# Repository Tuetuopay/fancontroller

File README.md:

# FanController

*Creative naming?* What is this?

Rheobus project rooted from a simple problem: all my PC fans are DC only (the
three wire kind), but my motherboard only supports PWM*. And why buy a
commercial one? Let's make my own!

*Even if it does, shhhh! This is a good excuse for a project!

## Hardware

Simple PCB designed with Eagle. It can control up to 8 fans, with an STM32F103
as a brain. On the extra side, there is an LED for each channel, because
blinkenlights are cool. For communications, this is scarce: a USB port and
UART or I2C header.

The PCB is mostly finished, some refinements may be needed. It is well under
10cm x 10cm to be ordered on the cheap from the likes of DirtyPCB or JLCPCB.

All parts are SMD (except for headers and the one quartz), but do not go smaller
than 0603 resistors, easily solderable by hand. They can all be easily sourced
from Ebay.

## Software

This is not written yet. I plan on doing it with ChibiOS, just for kicks. It is
well supported on the STM32 platform, easy to use (once you accepted the fact
that documentation is almost nonexistent).

# Licence

```
THE BEER-WARE LICENSE (Revision 42):
tuetuopay at me dot com wrote this file. As long as you retain this notice you
can do whatever you want with this stuff. If we meet some day, and you think
this stuff is worth it, you can buy me a beer in return. Tuetuopay.
```

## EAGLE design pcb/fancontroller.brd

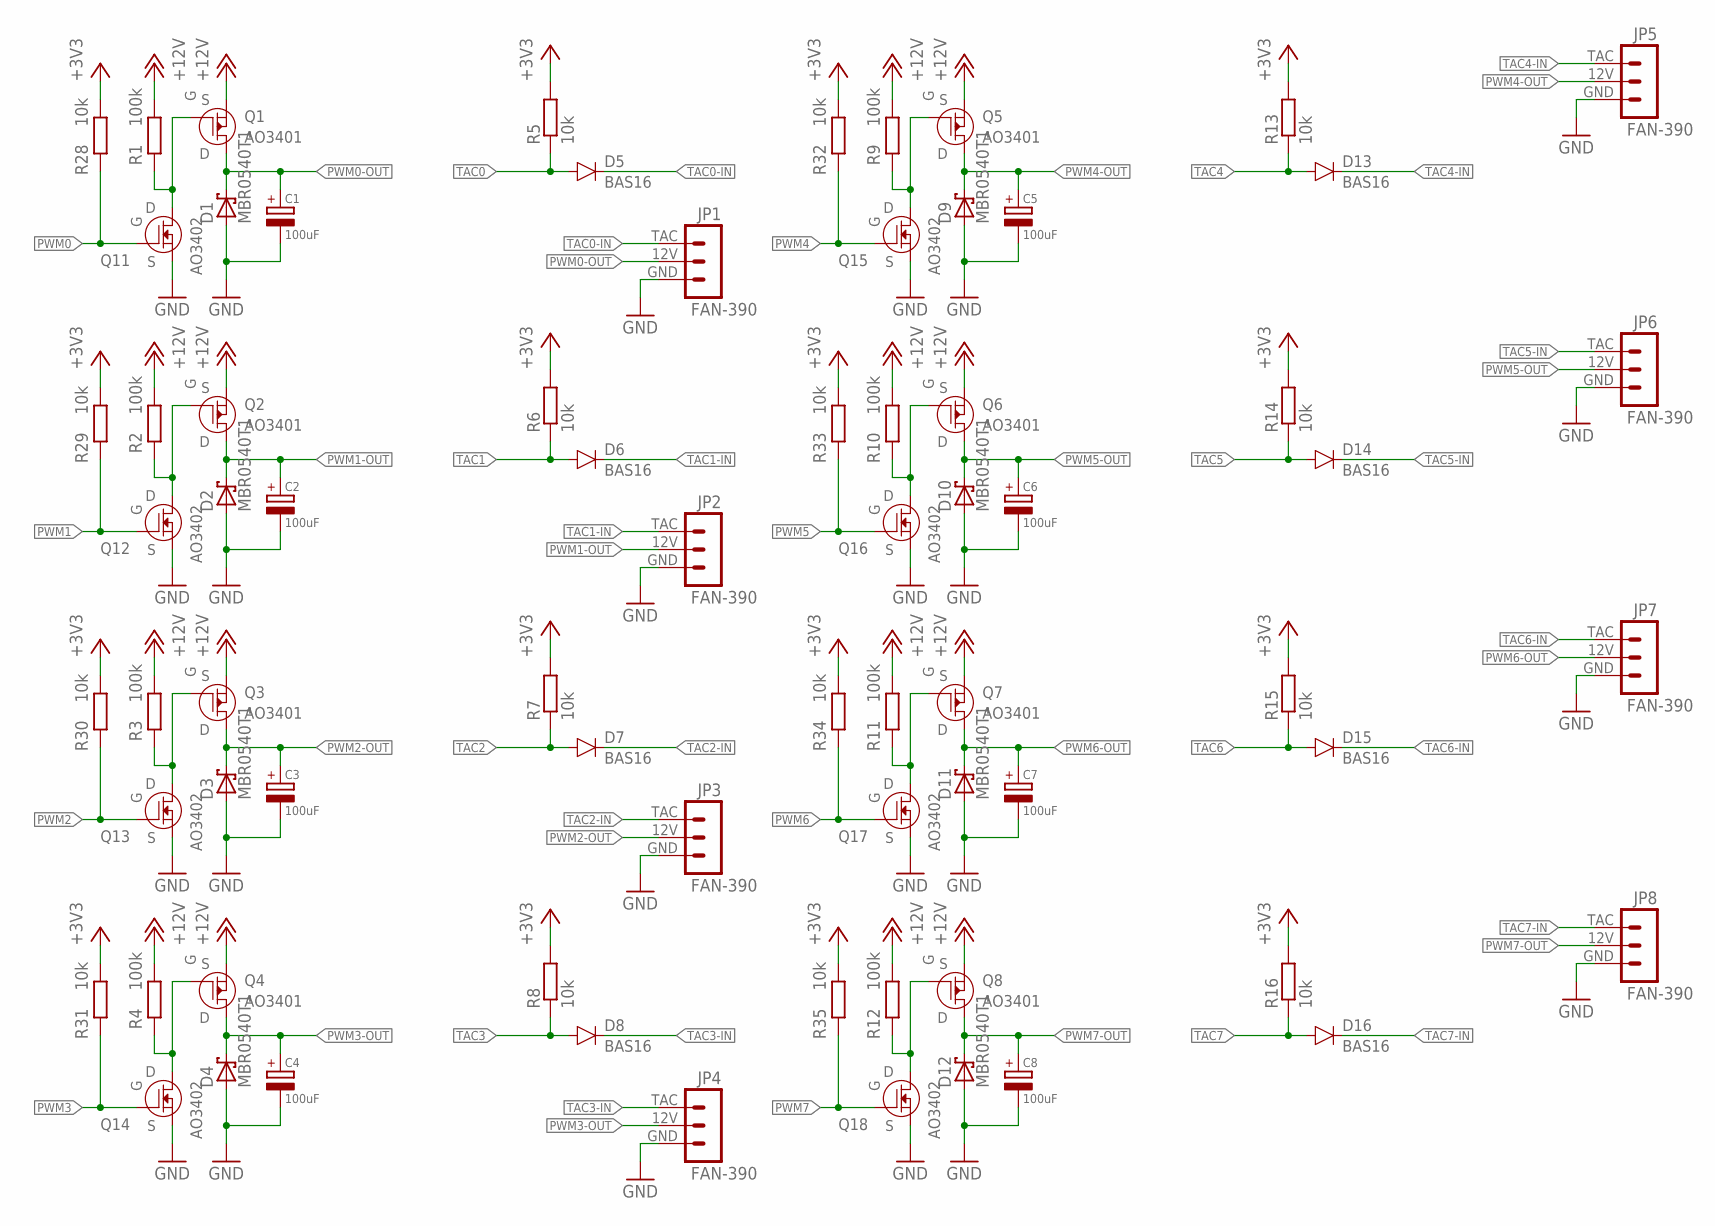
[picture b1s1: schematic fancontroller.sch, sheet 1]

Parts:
C1, C2, C3, C4, C5, C6, C7, C8: 100uF; CAP-D6.3
D1, D2, D3, D4, D9, D10, D11, D12: MBR0540T1; SOD123
D5, D6, D7, D8, D13, D14, D15, D16: BAS16; SOT23-3
JP1, JP2, JP3, JP4, JP5, JP6, JP7, JP8: FAN-390; FAN-3PIN/90
Q1, Q2, Q3, Q4, Q5, Q6, Q7, Q8: AO3401; SOT23-3
Q11, Q12, Q13, Q14, Q15, Q16, Q17, Q18: AO3402; SOT23-3
R1, R2, R3, R4, R9, R10, R11, R12: 100k; R0603
R5, R6, R7, R8, R13, R14, R15, R16, R28, R29, R30, R31, R32, R33, R34, R35: 10k; R0603

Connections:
+3V3: R5.2, R6.2, R7.2, R8.2, R13.2, R14.2, R15.2, R16.2, R28.2, R29.2, R30.2, R31.2, R32.2, R33.2, R34.2, R35.2; also elsewhere on the board
+12V: Q1.2 (S), Q2.2 (S), Q3.2 (S), Q4.2 (S), Q5.2 (S), Q6.2 (S), Q7.2 (S), Q8.2 (S), R1.2, R2.2, R3.2, R4.2, R9.2, R10.2, R11.2, R12.2; also elsewhere on the board
GND: C1.N (NEG), C2.N (NEG), C3.N (NEG), C4.N (NEG), C5.N (NEG), C6.N (NEG), C7.N (NEG), C8.N (NEG), D1.A, D2.A, D3.A, D4.A, D9.A, D10.A, D11.A, D12.A, JP1.GND (1), JP2.GND (1), JP3.GND (1), JP4.GND (1), JP5.GND (1), JP6.GND (1), JP7.GND (1), JP8.GND (1), Q11.2 (S), Q12.2 (S), Q13.2 (S), Q14.2 (S), Q15.2 (S), Q16.2 (S), Q17.2 (S), Q18.2 (S); also elsewhere on the board
PWM0: Q11.1 (G), R28.1; also elsewhere on the board
PWM0-1: Q1.1 (G), Q11.3 (D), R1.1
PWM0-OUT: C1.P (POS), D1.C, JP1.12V (2), Q1.3 (D)
PWM1: Q12.1 (G), R29.1; also elsewhere on the board
PWM1-1: Q2.1 (G), Q12.3 (D), R2.1
PWM1-OUT: C2.P (POS), D2.C, JP2.12V (2), Q2.3 (D)
PWM2: Q13.1 (G), R30.1; also elsewhere on the board
PWM2-1: Q3.1 (G), Q13.3 (D), R3.1
PWM2-OUT: C3.P (POS), D3.C, JP3.12V (2), Q3.3 (D)
PWM3: Q14.1 (G), R31.1; also elsewhere on the board
PWM3-1: Q4.1 (G), Q14.3 (D), R4.1
PWM3-OUT: C4.P (POS), D4.C, JP4.12V (2), Q4.3 (D)
PWM4: Q15.1 (G), R32.1; also elsewhere on the board
PWM4-1: Q5.1 (G), Q15.3 (D), R9.1
PWM4-OUT: C5.P (POS), D9.C, JP5.12V (2), Q5.3 (D)
PWM5: Q16.1 (G), R33.1; also elsewhere on the board
PWM5-1: Q6.1 (G), Q16.3 (D), R10.1
PWM5-OUT: C6.P (POS), D10.C, JP6.12V (2), Q6.3 (D)
PWM6: Q17.1 (G), R34.1; also elsewhere on the board
PWM6-1: Q7.1 (G), Q17.3 (D), R11.1
PWM6-OUT: C7.P (POS), D11.C, JP7.12V (2), Q7.3 (D)
PWM7: Q18.1 (G), R35.1; also elsewhere on the board
PWM7-1: Q8.1 (G), Q18.3 (D), R12.1
PWM7-OUT: C8.P (POS), D12.C, JP8.12V (2), Q8.3 (D)
TAC0: D5.1 (A), R5.1; also elsewhere on the board
TAC0-IN: D5.3 (C), JP1.TAC (3)
TAC1: D6.1 (A), R6.1; also elsewhere on the board
TAC1-IN: D6.3 (C), JP2.TAC (3)
TAC2: D7.1 (A), R7.1; also elsewhere on the board
TAC2-IN: D7.3 (C), JP3.TAC (3)
TAC3: D8.1 (A), R8.1; also elsewhere on the board
TAC3-IN: D8.3 (C), JP4.TAC (3)
TAC4: D13.1 (A), R13.1; also elsewhere on the board
TAC4-IN: D13.3 (C), JP5.TAC (3)
TAC5: D14.1 (A), R14.1; also elsewhere on the board
TAC5-IN: D14.3 (C), JP6.TAC (3)
TAC6: D15.1 (A), R15.1; also elsewhere on the board
TAC6-IN: D15.3 (C), JP7.TAC (3)
TAC7: D16.1 (A), R16.1; also elsewhere on the board
TAC7-IN: D16.3 (C), JP8.TAC (3)

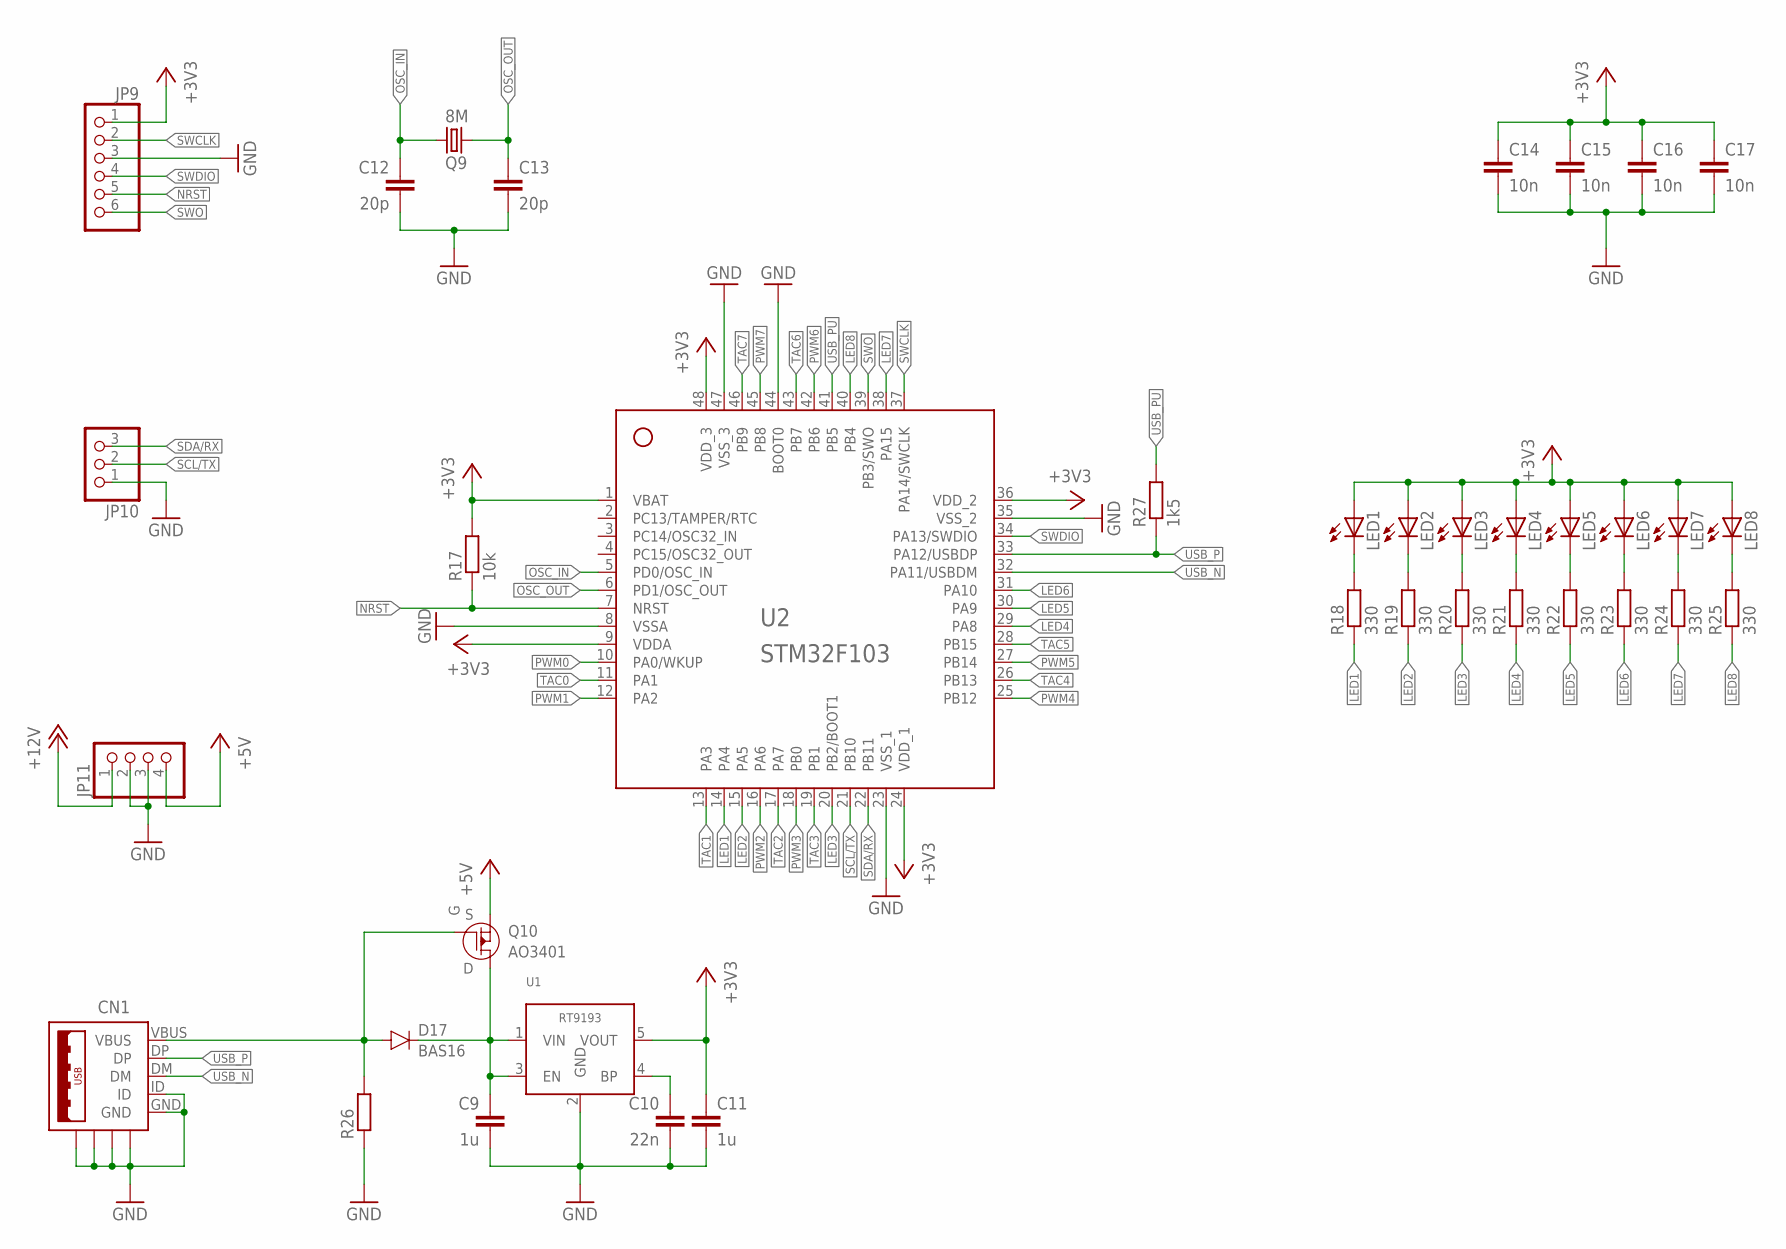
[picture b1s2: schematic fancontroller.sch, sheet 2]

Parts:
C9, C11: 1u; 0603
C10: 22n; 0603
C12, C13: 20p; 0603
C14, C15, C16, C17: 10n; 0603
CN1: USB-MICROB-2TABS; USB-MICROB-2
D17: BAS16; SOT23-3
JP9: PINHD-1X6; 1X06
JP10: PINHD-1X3/90; 1X03/90
JP11: PINHD-1X4/90; 1X04/90
LED1, LED2, LED3, LED4, LED5, LED6, LED7, LED8: LEDSML0805; SML0805
Q9: 8M; HC49/S
Q10: AO3401; SOT23-3
R17: 10k; R0603
R18, R19, R20, R21, R22, R23, R24, R25: 330; R0603
R26: RR0603; R0603
R27: 1k5; R0603
U1: RT9193; SOT23-5
U2: STM32F103-48LQFP; LQFP-48

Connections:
+3V3: C11.1, C14.1, C15.1, C16.1, C17.1, JP9.1, LED1.A, LED2.A, LED3.A, LED4.A, LED5.A, LED6.A, LED7.A, LED8.A, R17.2, U1.5 (VOUT), U2.1 (VBAT), U2.9 (VDDA), U2.24 (VDD_1), U2.36 (VDD_2), U2.48 (VDD_3); also elsewhere on the board
+5V: JP11.4, Q10.2 (S)
+12V: JP11.1; also elsewhere on the board
GND: C9.2, C10.2, C11.2, C12.2, C13.2, C14.2, C15.2, C16.2, C17.2, CN1.GND, CN1.GND@1 (GND), CN1.GND@2 (GND), CN1.GND@3 (GND), CN1.GND@4 (GND), CN1.ID, JP9.3, JP10.1, JP11.2, JP11.3, R26.1, U1.2 (GND), U2.8 (VSSA), U2.23 (VSS_1), U2.35 (VSS_2), U2.44 (BOOT0), U2.47 (VSS_3); also elsewhere on the board
LED1: R18.1, U2.14 (PA4)
LED2: R19.1, U2.15 (PA5)
LED3: R20.1, U2.20 (PB2/BOOT1)
LED4: R21.1, U2.29 (PA8)
LED5: R22.1, U2.30 (PA9)
LED6: R23.1, U2.31 (PA10)
LED7: R24.1, U2.38 (PA15)
LED8: R25.1, U2.40 (PB4)
unnamed: LED3.C, R20.2
unnamed: LED2.C, R19.2
unnamed: LED1.C, R18.2
unnamed: LED4.C, R21.2
unnamed: LED7.C, R24.2
unnamed: LED8.C, R25.2
unnamed: LED5.C, R22.2
unnamed: LED6.C, R23.2
unnamed: C10.1, U1.4 (BP)
NRST: JP9.5, R17.1, U2.7 (NRST)
OSC_IN: C12.1, Q9.1, U2.5 (PD0/OSC_IN)
OSC_OUT: C13.1, Q9.2, U2.6 (PD1/OSC_OUT)
PWM0: U2.10 (PA0/WKUP); also elsewhere on the board
PWM1: U2.12 (PA2); also elsewhere on the board
PWM2: U2.16 (PA6); also elsewhere on the board
PWM3: U2.18 (PB0); also elsewhere on the board
PWM4: U2.25 (PB12); also elsewhere on the board
PWM5: U2.27 (PB14); also elsewhere on the board
PWM6: U2.42 (PB6); also elsewhere on the board
PWM7: U2.45 (PB8); also elsewhere on the board
SCL/TX: JP10.2, U2.21 (PB10)
SDA/RX: JP10.3, U2.22 (PB11)
SWCLK: JP9.2, U2.37 (PA14/SWCLK)
SWDIO: JP9.4, U2.34 (PA13/SWDIO)
SWO: JP9.6, U2.39 (PB3/SWO)
TAC0: U2.11 (PA1); also elsewhere on the board
TAC1: U2.13 (PA3); also elsewhere on the board
TAC2: U2.17 (PA7); also elsewhere on the board
TAC3: U2.19 (PB1); also elsewhere on the board
TAC4: U2.26 (PB13); also elsewhere on the board
TAC5: U2.28 (PB15); also elsewhere on the board
TAC6: U2.43 (PB7); also elsewhere on the board
TAC7: U2.46 (PB9); also elsewhere on the board
USB_N: CN1.DM, U2.32 (PA11/USBDM)
USB_P: CN1.DP, R27.1, U2.33 (PA12/USBDP)
USB_PU: R27.2, U2.41 (PB5)
VBUS: CN1.VBUS, D17.1 (A), Q10.1 (G), R26.2
VIN: C9.1, D17.3 (C), Q10.3 (D), U1.1 (VIN), U1.3 (EN)

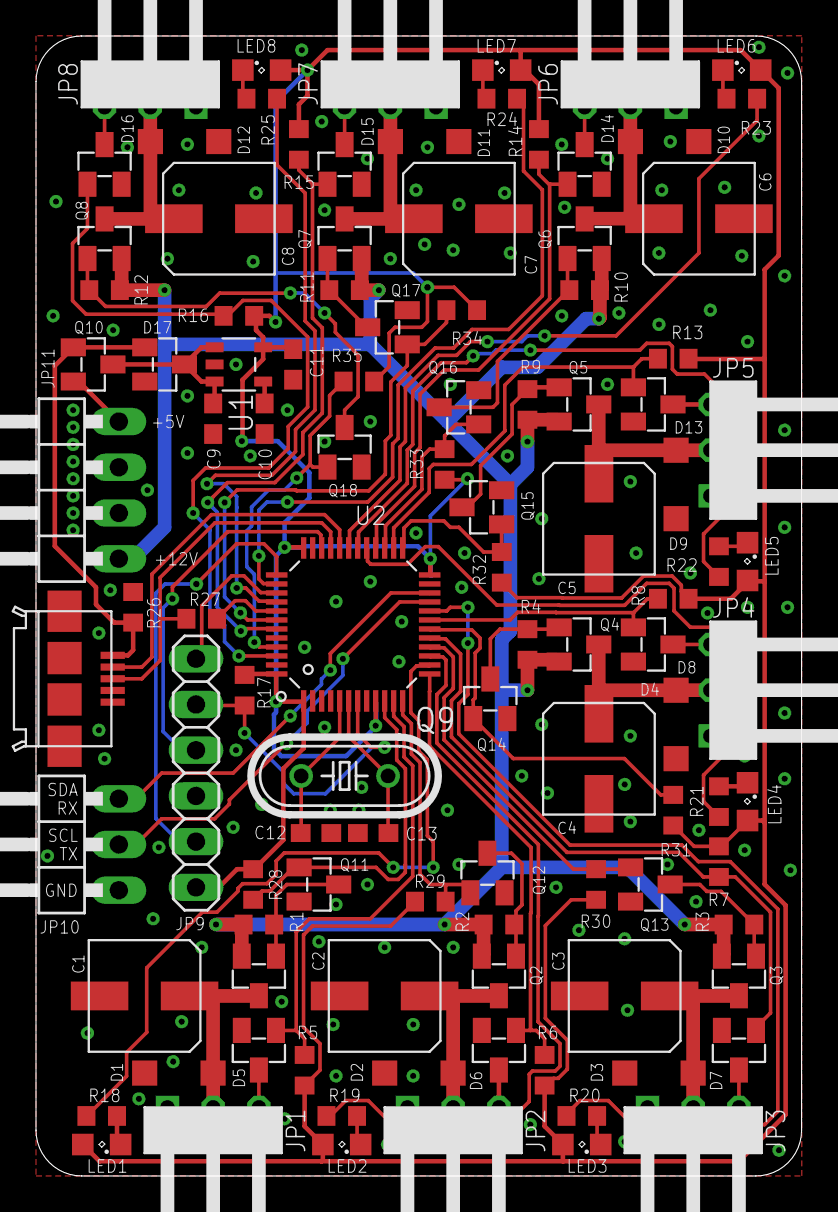
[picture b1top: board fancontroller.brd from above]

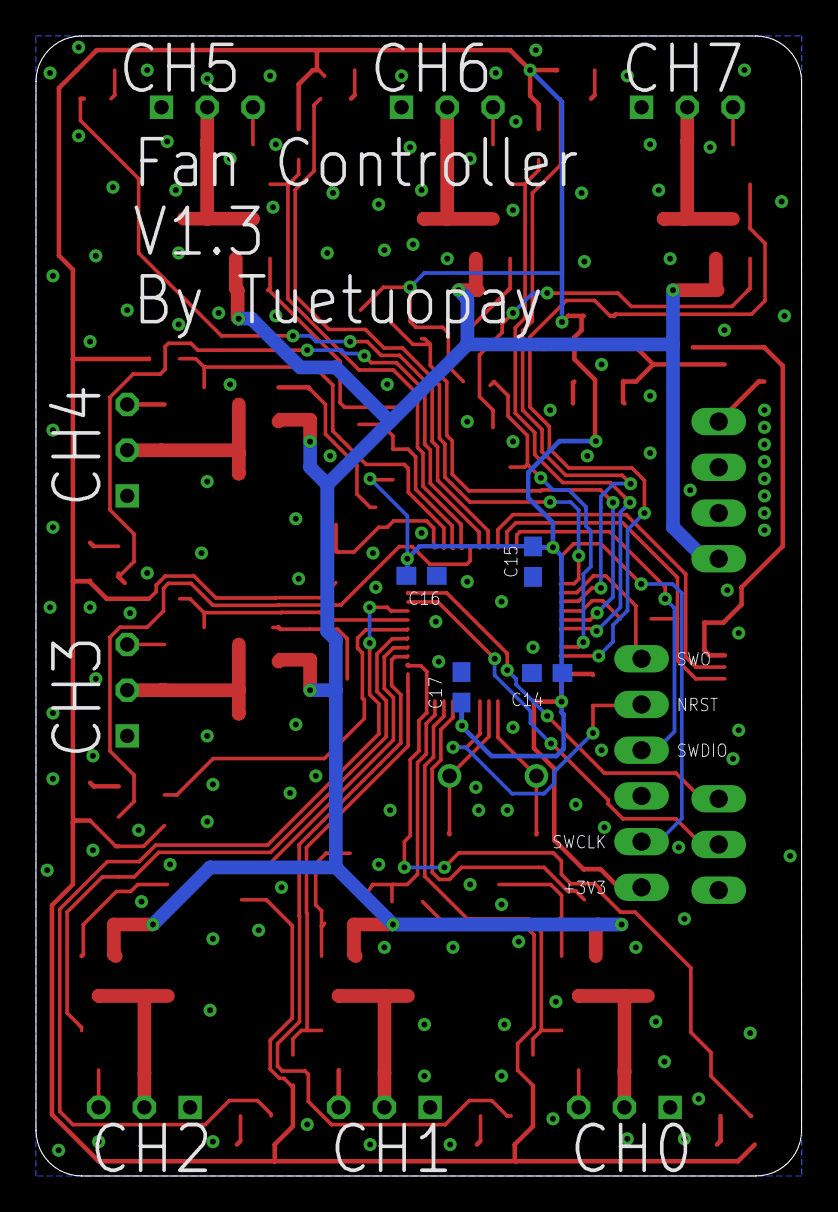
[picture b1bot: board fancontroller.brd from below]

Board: 2 copper layers, 42.5 x 63.3 mm, 109 parts (4 on the bottom side), 74 nets.

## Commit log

2018-05-10 Add README and LICENSE
2018-05-10 pcb: Add rev. 1.3
2018-05-11 firmware: Initial draft version
2018-05-11 fw: Add USB shell
2018-05-11 fw: Add serial shell
2018-05-11 fw: Add USB pullup for next board revision
2018-05-11 pcb: Connect USB pull-up resistor to GPIO
2018-05-11 pcb: Move header silkscreen to top
2018-05-11 pcb: Move misc designators for better readability
2018-05-12 fw: Add LED driver
2018-05-12 fw: Add led shell command
2018-05-12 fw: Add PWM driver for the fans
